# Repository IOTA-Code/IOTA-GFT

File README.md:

# IOTA-GFT Project
----------------------------
The IOTA-GFT project (IOTA GPS Flash Timer) implements a GPS based solution for adding UTC timestamps to sequential image captures (e.g. video).  The project includes both an IOTA-GFT hardware device and various software components for the computer used to capture the video data.

The IOTA-GFT device connects to the video recording computer and drives an LED which is attached to the front of the optics.  The IOTA-GFT software on the recording computer controls the LED flash sequence from the device and logs the timing information from the IOTA-GFT device.  After recording a video sequence, this recording computer IOTA-GFT software analyzes the video and timing log to determine the times for each video frame.

This repository includes the following components:
- IOTA-GFT Device
    - Device Firmware
    - IOTA-GFT Shield PCB design
    - LED bracket components
- Recording computer software ( *** NOT YET ADDED TO THIS REPO ! )
    - ASCOM Driver for the IOTA-GFT device
    - FileStamper utility for inserting timestamps
- Documentation
    - Usage Guide(s) - also TBD !

## Licensing
------------
 This program is free software: you can redistribute it under the terms of the GNU General Public License as published by the Free Software Foundation, either version 3 of the License, or (at your option) any later version.  However, if you wish to make modifications, we add a further restriction.  If you make changes to the code from this repository, you must agree to NOT use the modified code for timing occultation observations.

 This program is distributed in the hope that it will be useful, but WITHOUT ANY WARRANTY; without even the implied warranty of MERCHANTABILITY or FITNESS FOR A PARTICULAR PURPOSE.  See the GNU General Public License for more details.

## Developers & Contributors
----------------------------

- Bob Anderson
- Steve Preston

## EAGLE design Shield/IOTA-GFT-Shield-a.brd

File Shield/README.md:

# IOTA-GFT Shield
----------------------------
The IOTA-GFT Arduino shield includes the GPS receiver and driver circuit for the LED.  This shield is designed for and requires an Arduino Mega 2560 R3 board.  The IOTA-GFT controller consists of this shield mounted on an Arduino Mega.  This repository carries the Eagle design files for the shield.

## Components
--------------
- IOTA-GFT shield PCB
- Female stacking headers for Arduino Mega ( https://a.co/d/8ICgdAu )
- GT-U7 GPS breakout board based on ublox GPS receiver (https://a.co/d/9eoqRfC) 
- Active GPS Antenna + pigtail ( https://a.co/d/hI4Iglh )
- SparkFun Voltage-Level Translator Breakout - TXB0104 ( https://www.sparkfun.com/products/11771 )
- (2) seven pin male headers - 0.1" (can break off from longer header : https://a.co/d/7kpX5g9 )
- (1) six pin male header - 0.1"
- (2) JST-XH PCB jack , CONN HEADER VERT 2POS 2.5MM, JST part# B2B-XH-A ( https://www.digikey.com/short/nwvmtq8r )
- Resistors (1/4w)
  - (1) 150 ohm
  - (1) 1k ohm
  - (1) 5.6k ohm
  - (1) 200k ohm
- Capacitors (50v)
  - (1) 30 pf
- Transistors
  - (1) 2N3906
- Plastic zip tie (4")

## Schematic and Board layout
------------

## Assembly
------------
- Solder the Arduino shield stacking headers onto the PCB.
- Solder the two 7 pin male headers onto the PCB at the location of U2 (level shifter)
- Solder the one 6 pin male header onto the PCB at the location of the pins for the GT-U7 breakout board.
- Solder the resistors, capacitor, and transitor onto the PCB at the marked locations.
- Solder the two JST connectors onto the PCB with the open side facing away from the Arduino's USB and power connectors.
- Solder the TXB0104 breakout board onto the two male headers with the OE marked end facing the two JST connectors.
- Attach the GPS antenna pigtail to the antenna connector on the GT-U7 breakout board.
- Solder the GT-U7 GPS breakout board to the single six pin male header.
- Snug down the GPS antenna pigtail to the breakout board using the plastic zip tie.

## Licensing
------------
 This design is free: you can redistribute it under the terms of the GNU General Public License as published by the Free Software Foundation, either version 3 of the License, or (at your option) any later version.  However, if you wish to make modifications, we add a further restriction.  If you are going to use this design to measure times for occultation observations, you must agree to not modify the design.

 This design is distributed in the hope that it will be useful, but WITHOUT ANY WARRANTY; without even the implied warranty of MERCHANTABILITY or FITNESS FOR A PARTICULAR PURPOSE.  See the GNU General Public License for more details.

## Developers & Contributors
----------------------------
- Bob Anderson
- Steve Preston
- Aart Olsen

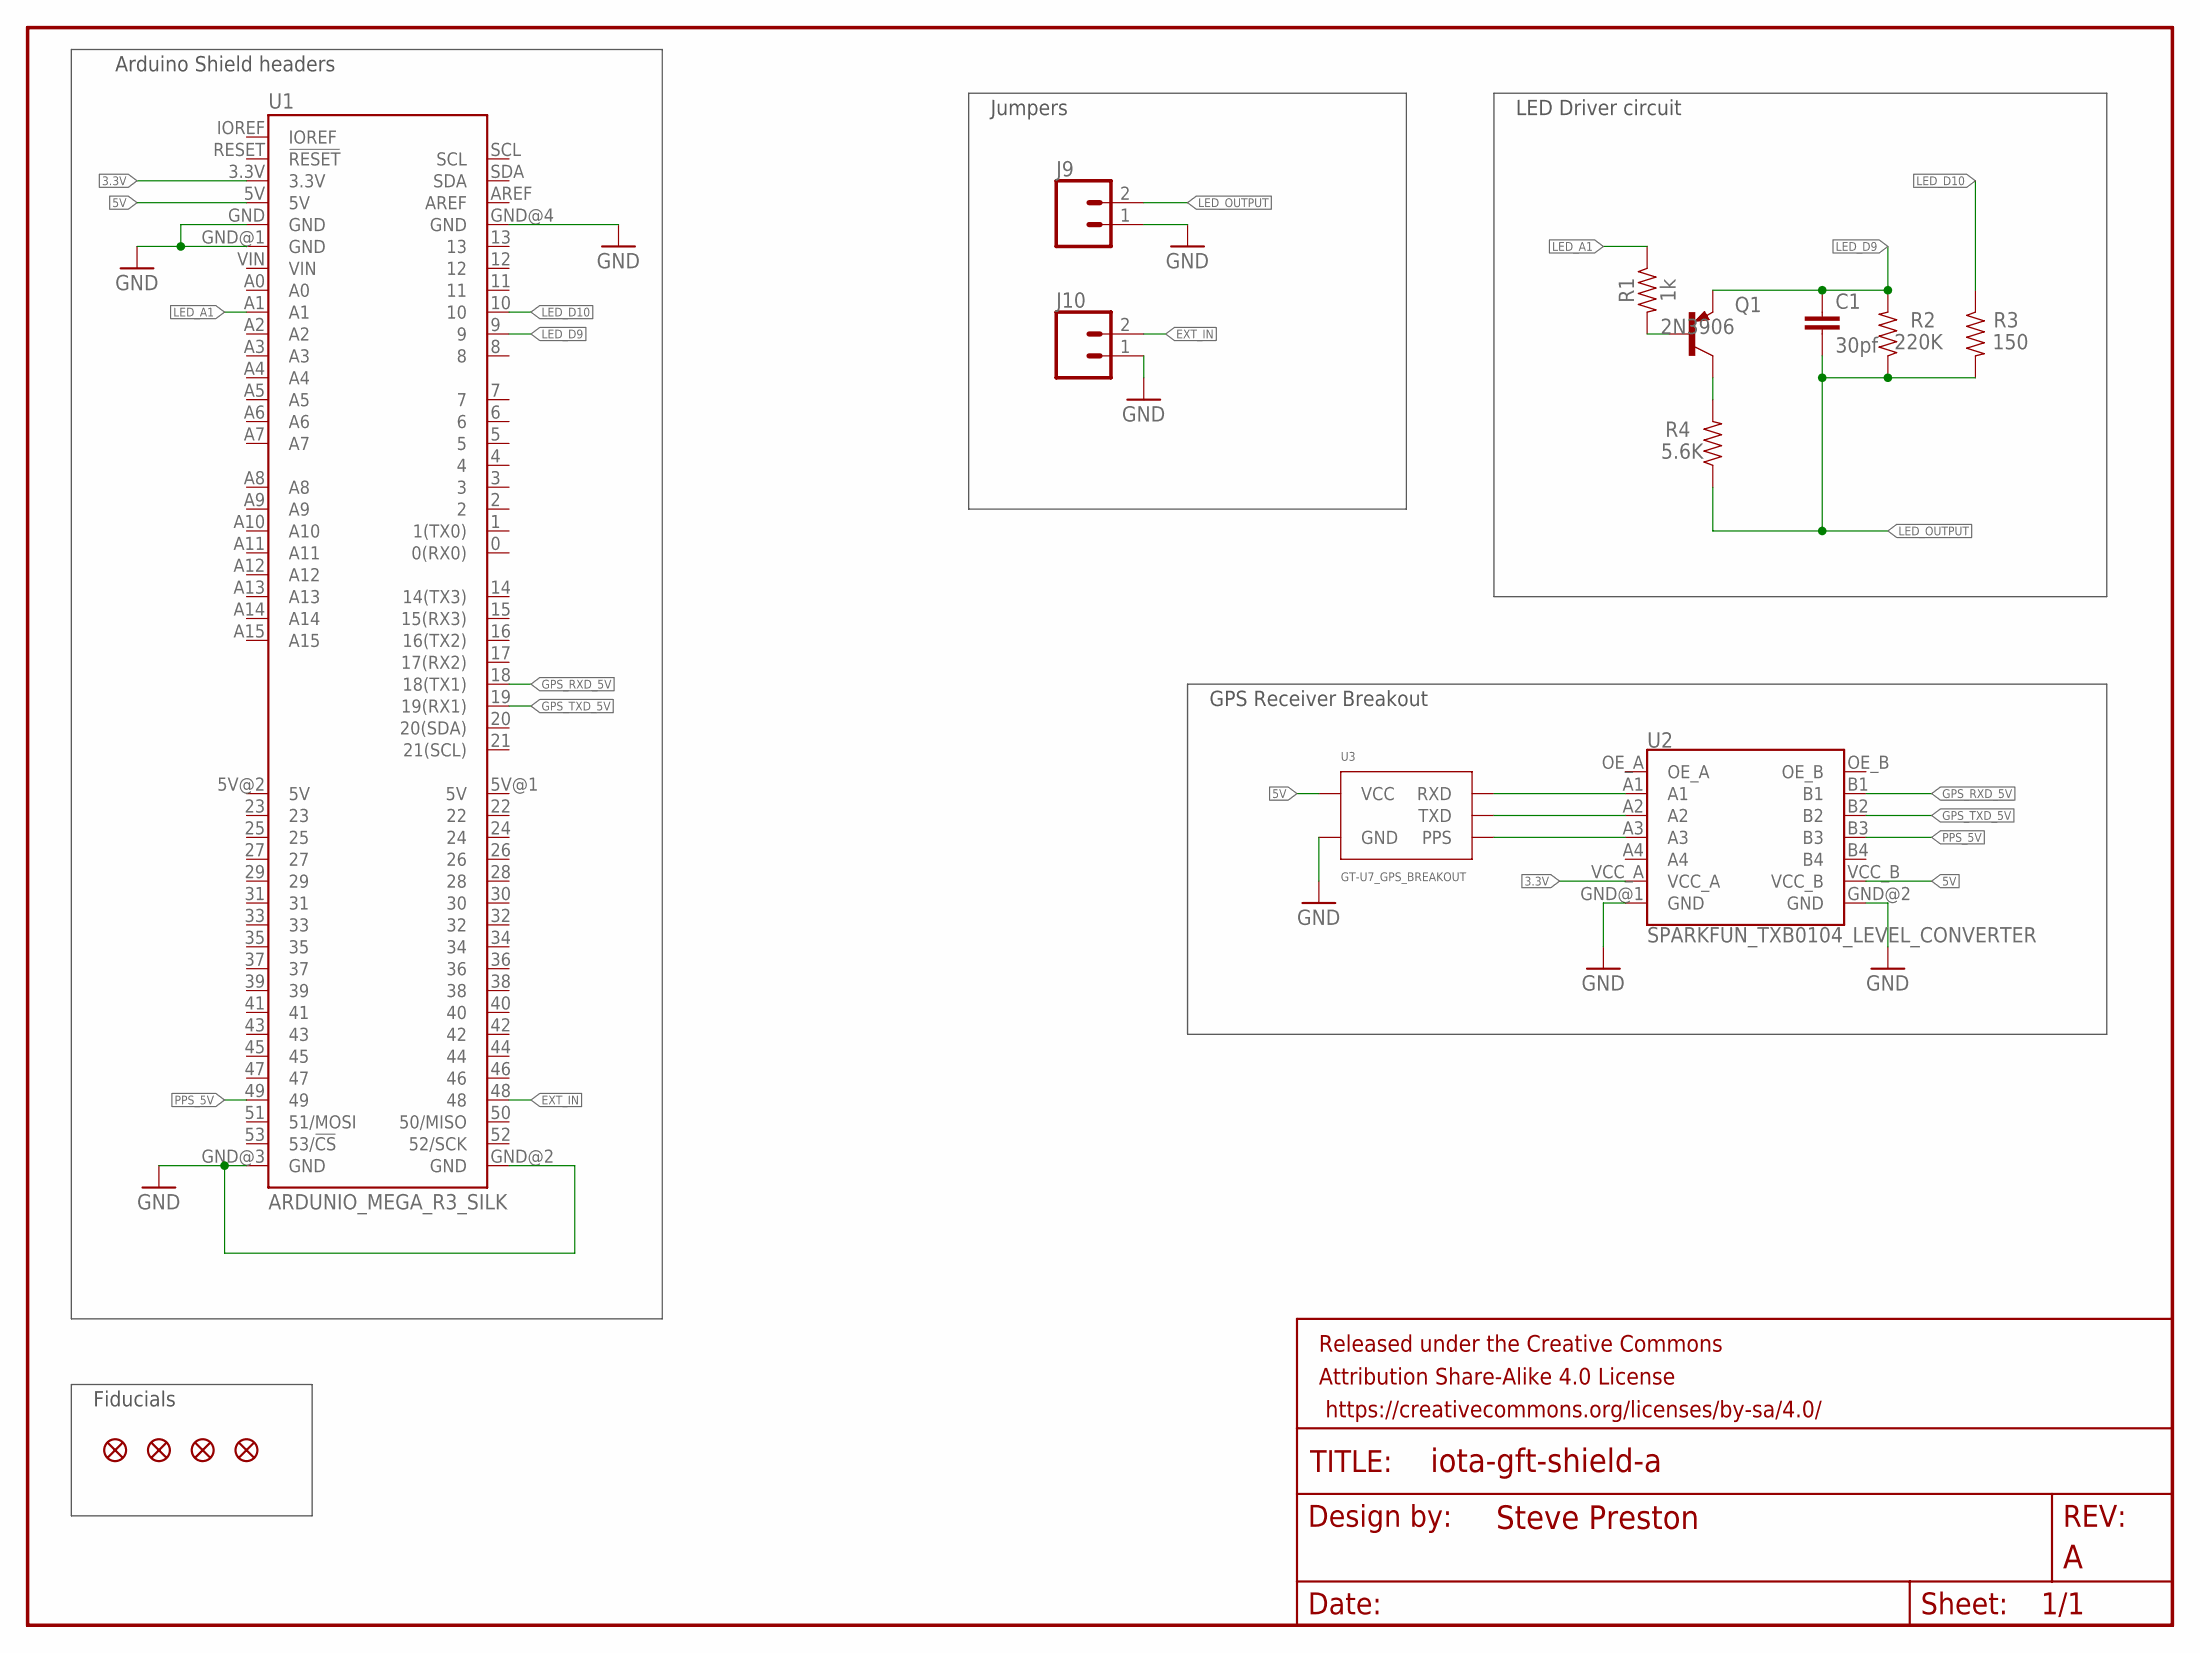
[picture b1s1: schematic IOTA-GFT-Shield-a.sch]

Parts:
C1: 30pf; CAP-PTH-5MM
FD1, FD2, FD3, FD4: FIDUCIALUFIDUCIAL; FIDUCIAL-MICRO
FRAME1: FRAME-LETTER; CREATIVE_COMMONS
J9, J10: CONN_02; 1X02
Q1: 2N3906; TO92
R1: 1k; AXIAL-0.3
R2: 220K; AXIAL-0.3
R3: 150; AXIAL-0.3
R4: 5.6K; AXIAL-0.3
U1: ARDUNIO_MEGA_R3_SILK; ARDUINO_MEGA_SILK
U2: SPARKFUN_TXB0104_LEVEL_CONVERTER; TXB0104_LEVEL_CONVERTER
U3: GT-U7_GPS_BREAKOUT; GT-UT

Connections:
3.3V: U1.3.3V, U2.VCC_A
5V: U1.5V, U2.VCC_B, U3.VCC
EXT_IN: J10.2, U1.48
GND: J9.1, J10.1, U1.GND, U1.GND@1 (GND), U1.GND@2 (GND), U1.GND@3 (GND), U1.GND@4 (GND), U2.GND@1 (GND), U2.GND@2 (GND), U3.GND
GPS_RXD: U2.A1, U3.RXD
GPS_RXD_5V: U1.18 (18(TX1)), U2.B1
GPS_TXD: U2.A2, U3.TXD
GPS_TXD_5V: U1.19 (19(RX1)), U2.B2
LED_A1: R1.P$1 (1), U1.A1
LED_D9: C1.1, Q1.3 (E), R2.P$2 (2), U1.9
LED_D10: R3.P$1 (1), U1.10
LED_OUTPUT: C1.2, J9.2, R2.P$1 (1), R3.P$2 (2), R4.P$1 (1)
unnamed: Q1.1 (C), R4.P$2 (2)
unnamed: Q1.2 (B), R1.P$2 (2)
PPS: U2.A3, U3.PPS
PPS_5V: U1.49, U2.B3

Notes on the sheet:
Jumpers
LED Driver circuit
Arduino Shield headers
GPS Receiver Breakout
Fiducials

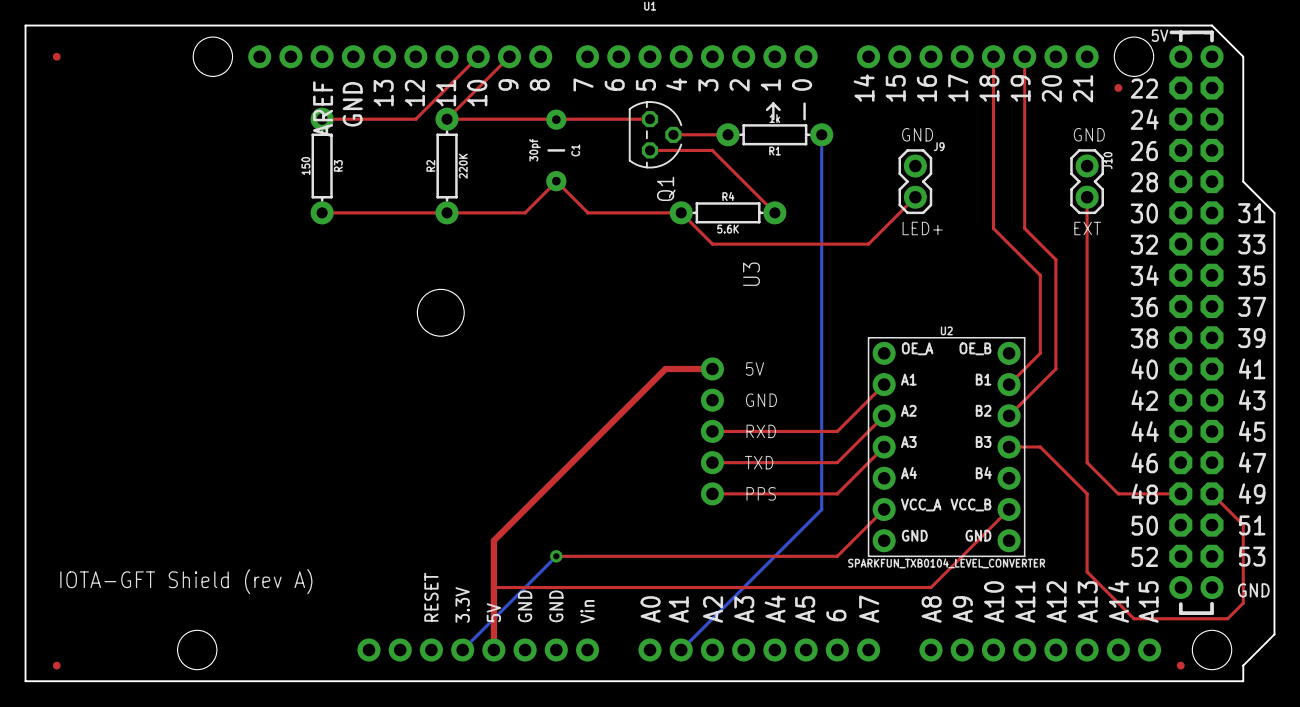
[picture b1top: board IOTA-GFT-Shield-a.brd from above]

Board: 2 copper layers, 101.6 x 53.3 mm, 16 parts (0 on the bottom side), 16 nets.

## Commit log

2022-10-12 A variety of changes toward manual mode
2022-10-12 updated GPS code to include NMEA parsing
2022-10-13 compiles but not yet ready for testing...
2022-10-14 Move several code segments to separate cpp/h files
2022-10-14 Added logging to serial for testing. Not tested yet.
2022-10-15 working version with PPS logging to serial port
2022-10-15 nmeaSentence logging to Serial
2022-10-18 added write to SD card.
2022-10-19 updates to logging. timestamp the file.
2022-10-19 added new files
2022-10-20 echo on command working
2022-10-22 flash Commands echo log file (list)
2023-01-08 various changes...
2023-01-09 A few updates
2023-01-10 checkpoint (added draft of EXP mode flashing)
2023-01-18 EXP mode seems to work... will need more testing
2023-02-27 I/O formatting changes change startup defaults - SD off various other...
2023-02-27 various changes
2023-04-06 checkpoint save before making changes
2023-11-24 various small changes...
2023-11-27 removed support for SD card, reworked USB commands
2023-11-29 modified code for flash ON/OFF to just set OCR2x registers
2023-11-30 cleaned up several compiler errors added error reporting
2023-12-01 only report NMEA errors while in TimeValid mode
2023-12-02 a few fixes
2023-12-02 added checksum test for NMEA sentences
2023-12-06 Errors move to WaitingForGPS mode (to avoid hang in Sync logic when not reseting time of RMC)
2024-03-02 Turn off SBAS, QZSS, and GLONASS
2024-03-03 more detailed error reporting for NMEA parsing
2024-03-03 update version number : )
2024-03-03 fixed error in GGA parser
2024-03-10 implement FlashMode = LED
2024-03-10 update version number
2024-03-10 LED ON/OFF : check for LED mode first
2024-03-10 remove LED Mode. LED ON/OFF now work in PPS mode or EXP mode.
2024-03-10 added checksum to log output
2024-03-11 checksums on response to device commands
2024-03-11 re-enable system interrupts in PPS and EXP ISRs
2024-03-11 re-enable interrupts in Timer3 output compare ISR
2024-03-11 add eagle project file
2024-03-11 added option checksum to device commands
2024-03-11 EXP ISR - re-enable ints AFTER starting LED
2024-03-11 new version number
2024-03-12 added checksum to a couple of messages. moved SendResponse to logger.cpp
2024-03-13 cleared interrupts around logging again to avoid interrupting logging sentences
2024-03-13 update version number and a few comments.
2024-03-13 fixed check of incoming checksum with commands. updated version number.
2024-03-15 allow flash level == 0
2024-04-01 bug fix: pps code was logging the time of the previous pps
2024-05-04 added/updated readme.md files
2024-05-04 more documentation revised board file of shield to put component values in tNames (silkscreen)
2024-07-25 documentation update
2024-08-24 Added Design.md documentation Cleaned up blnLog variables ... just blnLogEnable now.
2024-08-24 Update documentation
2024-09-12 update main Readme page
2025-04-08 Primarily changes to the sentences returned in response to a USB command to the device.
2025-10-13 changed Mode output sentence to include current status of LED
2025-10-13 update design.md document with change to Mode sentence
2025-10-25 small doc change IOTA-GFT.ino - remove unused variables and fixup check of tk_PPS
2025-10-25 Added the CLK flash mode. Passed initial testing...
2025-10-25 fixed init of timer 3 to clear compare interrupts by writing a 1 instead of 0 to TIFR3 bits

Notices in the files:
parts and their libraries:
SparkFun-Aesthetics: Licensing: Creative Commons ShareAlike 4.0 International - https://creativecommons.org/licenses/by-sa/4.0
SparkFun-Aesthetics: Released under the Creative Commons Attribution Share-Alike 4.0 License
SparkFun-Aesthetics: https://creativecommons.org/licenses/by-sa/4.0
